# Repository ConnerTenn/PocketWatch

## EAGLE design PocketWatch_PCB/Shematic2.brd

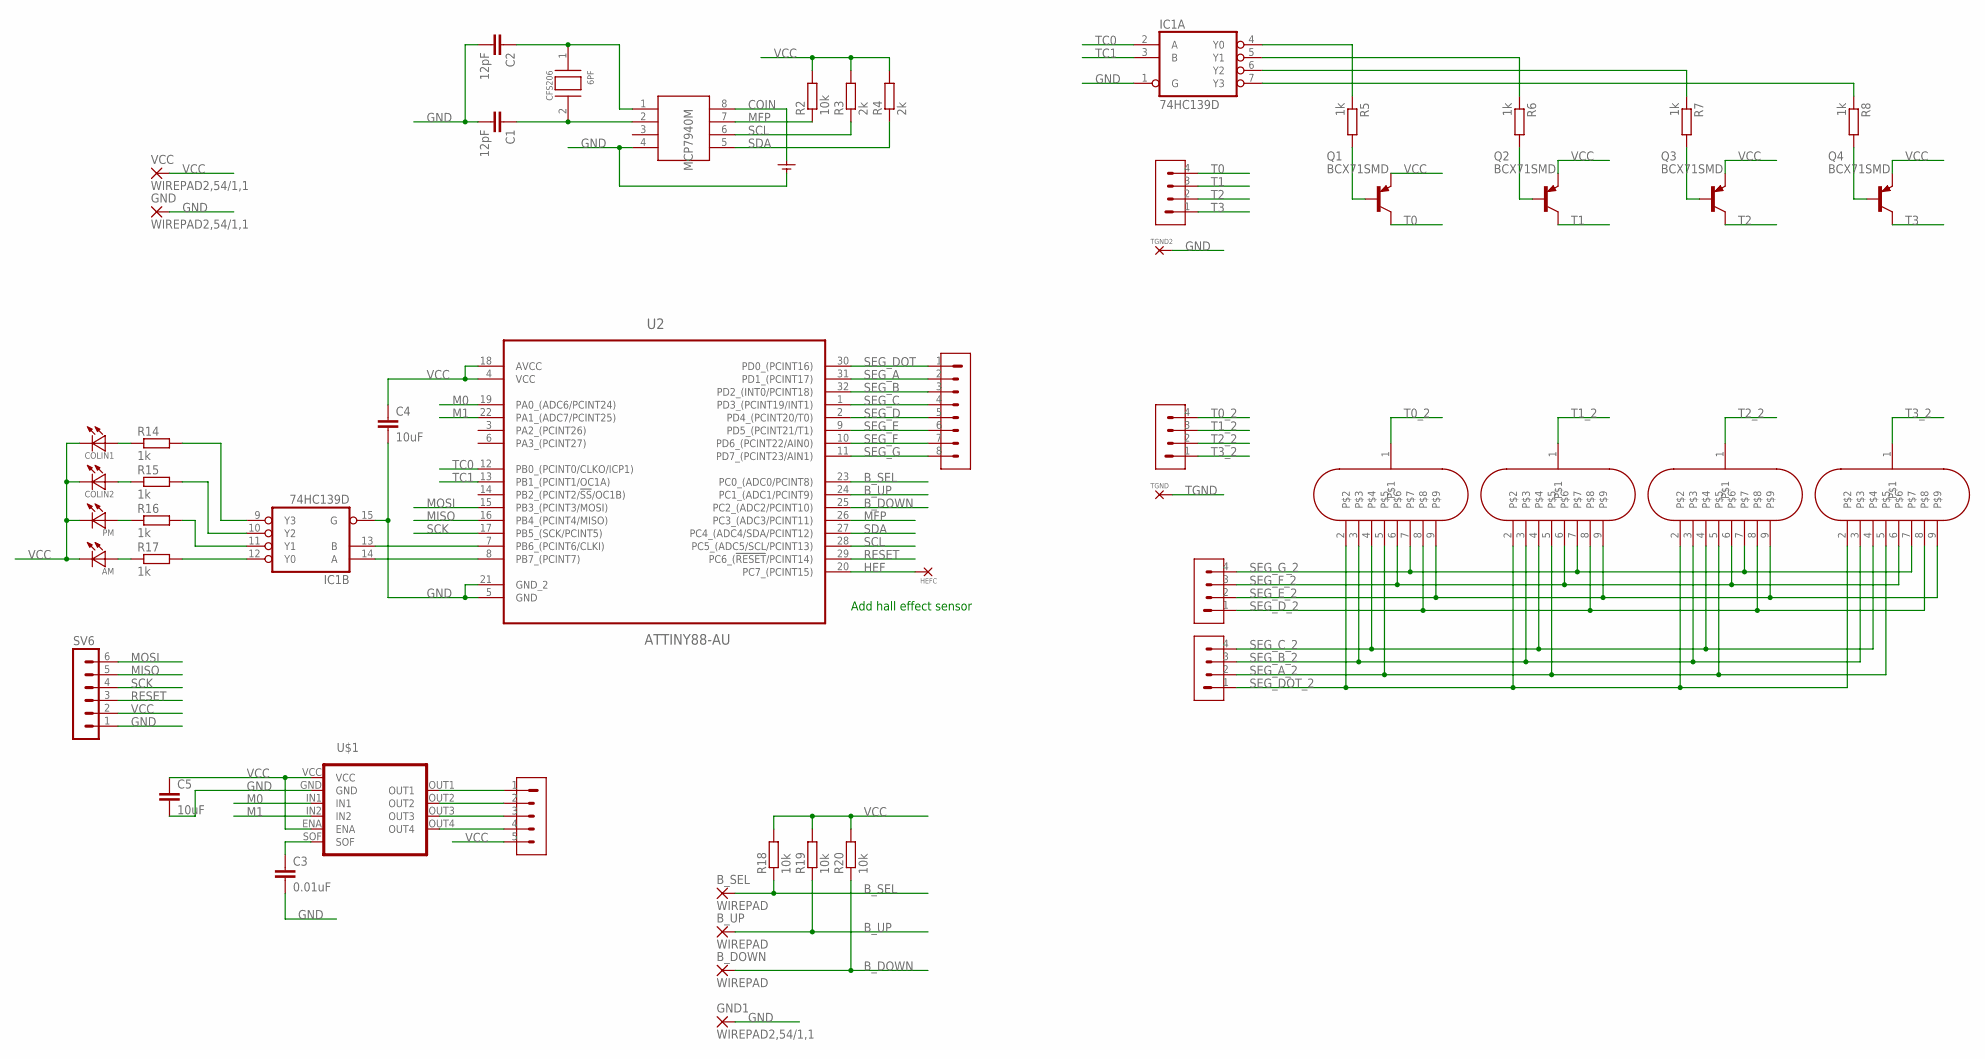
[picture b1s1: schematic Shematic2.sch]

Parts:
6PF: CFS206
AM: LED
B_DOWN: WIREPAD; 2,54/1,1
B_SEL: WIREPAD; 2,54/1,1
B_UP: WIREPAD; 2,54/1,1
C1, C2: 12pF; C1206
C3: 0.01uF; C1206
C4, C5: 10uF; C1206
COLIN1, COLIN2: LED
GND, GND1: WIREPAD2,54/1,1; 2,54/1,1
HEFC: H01
IC1: 74HC139D; SO16
MCP7940M: SOIC-8
PM: LED
Q1, Q2, Q3, Q4: BCX71SMD; SOT23
R2, R18, R19, R20: 10k; R1206
R3, R4: 2k; R1206
R5, R6, R7, R8, R14, R15, R16, R17: 1k; R1206
SV1: H08
SV2, SV3, SV5, SV7: H04
SV4: H05
SV6: MA06-1
TGND, TGND2: H01
TUBE0, TUBE1, TUBE2, TUBE3: IV-9
U2: ATTINY88-AU; QFP80P900X900X120-32N
U$1: LB1848MC
U$5: COIN
VCC: WIREPAD2,54/1,1; 2,54/1,1

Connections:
B_DOWN: B_DOWN.1, R20.1, U2.25 (PC2_(ADC2/PCINT10))
B_SEL: B_SEL.1, R18.1, U2.23 (PC0_(ADC0/PCINT8))
B_UP: B_UP.1, R19.1, U2.24 (PC1_(ADC1/PCINT9))
COIN: MCP7940M.8, U$5.V+
GND: C1.2, C2.2, C3.2, C4.2, C5.2, GND.1, GND1.1, IC1.1 (G), IC1.8 (GND), IC1.15 (G), MCP7940M.4, SV6.1, TGND2.P$1, U2.5 (GND), U2.21 (GND_2), U$1.GND, U$5.V-
HEF: HEFC.P$1, U2.20 (PC7_(PCINT15))
M0: U2.19 (PA0_(ADC6/PCINT24)), U$1.IN1
M1: U2.22 (PA1_(ADC7/PCINT25)), U$1.IN2
MFP: MCP7940M.7, R2.1, U2.26 (PC3_(ADC3/PCINT11))
MISO: SV6.5, U2.16 (PB4_(PCINT4/MISO))
MOSI: SV6.6, U2.15 (PB3_(PCINT3/MOSI))
unnamed: Q4.1 (B), R8.2
unnamed: Q3.1 (B), R7.2
unnamed: Q2.1 (B), R6.2
unnamed: 6PF.2, C1.1, MCP7940M.2
unnamed: Q1.1 (B), R5.2
unnamed: 6PF.1, C2.1, MCP7940M.1
unnamed: COLIN1.P$1, R14.1
unnamed: IC1.4 (Y0), R5.1
unnamed: COLIN2.P$1, R15.1
unnamed: IC1.5 (Y1), R6.1
unnamed: IC1.6 (Y2), R7.1
unnamed: PM.P$1, R16.1
unnamed: IC1.7 (Y3), R8.1
unnamed: AM.P$1, R17.1
unnamed: IC1.12 (Y0), R17.2
unnamed: IC1.11 (Y1), R16.2
unnamed: IC1.10 (Y2), R15.2
unnamed: IC1.9 (Y3), R14.2
unnamed: SV4.4, U$1.OUT4
unnamed: SV4.3, U$1.OUT3
unnamed: SV4.2, U$1.OUT2
unnamed: SV4.1, U$1.OUT1
unnamed: IC1.13 (B), U2.7 (PB6_(PCINT6/CLKI))
unnamed: IC1.14 (A), U2.8 (PB7_(PCINT7))
unnamed: C3.1, U$1.SOF
RESET: SV6.3, U2.29 (PC6_(!RESET!/PCINT14))
SCK: SV6.4, U2.17 (PB5_(SCK/PCINT5))
SCL: MCP7940M.6, R3.1, U2.28 (PC5_(ADC5/SCL/PCINT13))
SDA: MCP7940M.5, R4.1, U2.27 (PC4_(ADC4/SDA/PCINT12))
SEG_A: SV1.2, U2.31 (PD1_(PCINT17))
SEG_A_2: SV7.2, TUBE0.5, TUBE1.5, TUBE2.5, TUBE3.5
SEG_B: SV1.3, U2.32 (PD2_(INT0/PCINT18))
SEG_B_2: SV7.3, TUBE0.3, TUBE1.3, TUBE2.3, TUBE3.3
SEG_C: SV1.4, U2.1 (PD3_(PCINT19/INT1))
SEG_C_2: SV7.4, TUBE0.4, TUBE1.4, TUBE2.4, TUBE3.4
SEG_D: SV1.5, U2.2 (PD4_(PCINT20/T0))
SEG_DOT: SV1.1, U2.30 (PD0_(PCINT16))
SEG_DOT_2: SV7.1, TUBE0.2, TUBE1.2, TUBE2.2, TUBE3.2
SEG_D_2: SV2.1, TUBE0.8, TUBE1.8, TUBE2.8, TUBE3.8
SEG_E: SV1.6, U2.9 (PD5_(PCINT21/T1))
SEG_E_2: SV2.2, TUBE0.9, TUBE1.9, TUBE2.9, TUBE3.9
SEG_F: SV1.7, U2.10 (PD6_(PCINT22/AIN0))
SEG_F_2: SV2.3, TUBE0.6, TUBE1.6, TUBE2.6, TUBE3.6
SEG_G: SV1.8, U2.11 (PD7_(PCINT23/AIN1))
SEG_G_2: SV2.4, TUBE0.7, TUBE1.7, TUBE2.7, TUBE3.7
T0: Q1.3 (C), SV5.4
T0_2: SV3.4, TUBE0.1
T1: Q2.3 (C), SV5.3
T1_2: SV3.3, TUBE1.1
T2: Q3.3 (C), SV5.2
T2_2: SV3.2, TUBE2.1
T3: Q4.3 (C), SV5.1
T3_2: SV3.1, TUBE3.1
TC0: IC1.2 (A), U2.12 (PB0_(PCINT0/CLKO/ICP1))
TC1: IC1.3 (B), U2.13 (PB1_(PCINT1/OC1A))
TGND: TGND.P$1
VCC: AM.P$2, C4.1, C5.1, COLIN1.P$2, COLIN2.P$2, IC1.16 (VCC), PM.P$2, Q1.2 (E), Q2.2 (E), Q3.2 (E), Q4.2 (E), R2.2, R3.2, R4.2, R18.2, R19.2, R20.2, SV4.5, SV6.2, U2.4 (VCC), U2.18 (AVCC), U$1.ENA, U$1.VCC, VCC.1

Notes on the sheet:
Add hall effect sensor

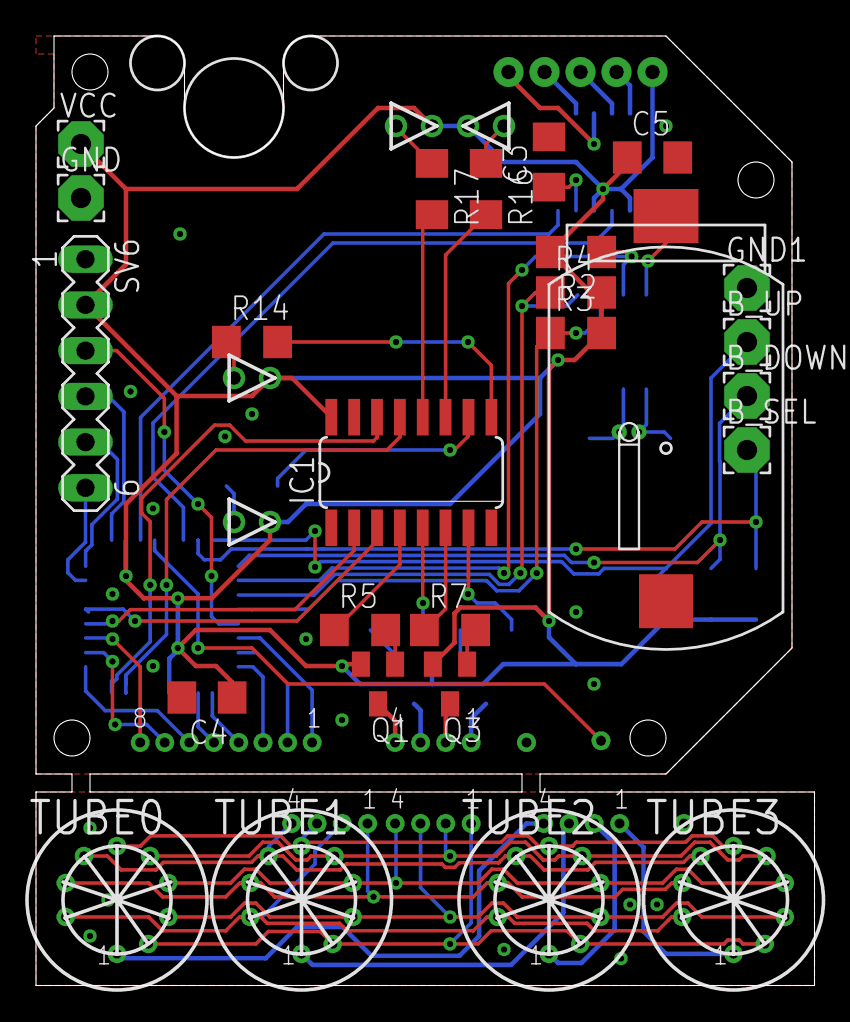
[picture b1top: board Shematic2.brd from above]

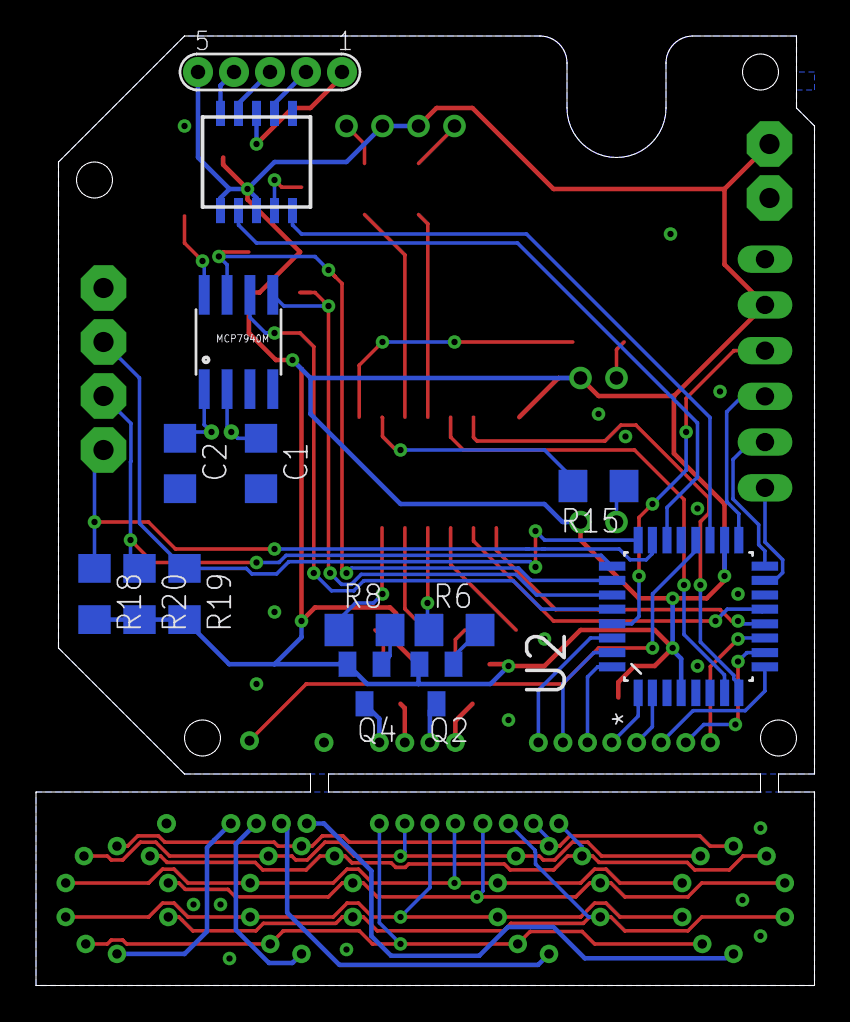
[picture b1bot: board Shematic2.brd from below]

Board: 2 copper layers, 43.2 x 52.8 mm, 53 parts (14 on the bottom side), 67 nets.

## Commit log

2018-05-01 Added .gitignore
2018-05-01 File Upload
2018-05-02 Added Dimensions
2018-05-02 Completed most of the routing
2018-05-02 Completed PCB layout. Passes DRC.
2018-05-02 Added drill holes
2018-05-03 Rearranged bottom board to be much more thin.
2018-05-03 Miscellaneous adjustments and ground plane fixes
2018-05-04 Added second version of the board for attempted board optimization
2018-05-04 Fixed H08. Added H05
2018-05-04 Schematic updates. Began component layout.
2018-05-08 File Update
2018-06-02 Swapped to using stepper motor driver. Routed board
2018-06-03 Added bypass capacitors. Revised routing.
2018-06-04 Created CAM job
2018-06-18 File update before redesign
